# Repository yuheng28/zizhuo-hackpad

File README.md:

# ZizhuoPad

## Overview

ZizhuoPad is a custom mechanical macropad with 6 keys and an OLED display.

It is designed to allow for easy hotswapping of the switches, and (maybe not as easy) key mapping modifications.

## Rationale

This is a project to build a custom mechanical macropad. The purpose of this project is to create a birthday gift for my friend, after whom this project is named.

As a technical challenge, I opted to write the firmware using AVR-C, instead of using Arduino or QMK. The PCB was designed using KiCAD, and the case was designed using Fusion 360.

## Hardware Summary

### Electronics
- Microcontroller: SparkFun Pro Micro (ATmega32U4)
- OLED Display: 128x32 pixel display
- Switches: 6 hotswappable mechanical switches (Akko Piano Switches)
- Connector: USB-C

### Case
- Material: PETG
- Infill: 75%
- Walls: 10 for Case, 5 for Lid
- Layer Height: 0.2mm

## Modifying the Software

In the `firmware` directory, a Microchip Studio project is included. You can open the `.atsln` file in Microchip Studio to build the firmware.

The firmware uses the LUFA library to implement USB HID functionality. The project was first developed using the LUFA library's keyboard example, so as to have the build environment set up and working. Then, the code was modified to implement the desired functionality for the macropad.

However, since these are all in the project files, the build environment is already set up and working.

To modify the key mappings, lines 292-325 in Keyboard.c can be modified by replacing the keycode macros with the appropriate keycodes from LUFA's HID usage tables.

To modify the animation on the OLED display, the lines 65-135 in OLED.c can be modified with the appropriate bytes to display the desired animation. The OLED display has a resolution of 128x32 pixel display. To generate the byte array for the animation, use [Javl's image2cpp tool](https://javl.github.io/image2cpp/). The relevant settings for the tool are:
- Canvas Size: 128x32
- Orientation: Vertical
- Invert pixels: Yes (alternatively, line 191 in Keyboard.c can be commented to invert the pixels)

The other settings can be left as their default values. The generated byte array can then be copied into lines 292-325 in Keyboard.c.

After building the firmware, the resulting `Keyboard.hex` file can be flashed to the ATmega32U4 microcontroller using avrdude.

To flash the microcontroller, it needs to first be put into bootloader mode. This can be done by shorting the reset pin to ground. For approximately 8 seconds after doing this, the microcontroller will be in bootloader mode and can be flashed using avrdude.

## Project Pictures

## Special Thanks

- [Boyce Ang Kok Hong (Hong Guo Feng)]() for helping with the design of the case, as well as providing help every step of the way.
- [HackClub](https://hackclub.com/) for inspiring this project
- [Javl's image2cpp tool](https://javl.github.io/image2cpp/) for generating the byte array for the OLED animation
- [LUFA library](https://www.fourwalledcubicle.com/LUFA.php) for providing the USB HID functionality
- [Sun Zizhuo](https://github.com/UnidentifiedX) for giving us a reason to make this project in the first place

## Bill of Materials
| **Name**                          | **Quantity** | **Price** | **Link**                                                                                                                                                     | **Distributor** |
|-----------------------------------|--------------|-----------|--------------------------------------------------------------------------------------------------------------------------------------------------------------|-----------------|
| 3D Printed Case                   | 1            | 0         |                                                                                                                                                              | Additive Inn    |
| USB C Cable                       | 1            | 0         |                                                                                                                                                              | Selleys         |
| Gateron Hot-swappable Key Sockets | 6            | 0         | https://shopee.sg/10-pcs-Gateron-Hot-swappable-PCB-Socket-Mechanical-Keyboard-DIY-Hot-Plug-Socket-For-Cherry-MX-Switch-i.890923955.26713298801               | Shopee          |
| Resistors (1k)                    | 2            | 0         | https://shopee.sg/1-PCS-or-10-PCS-of-Metal-Film-Resistors-1-4W-0.25W-1-10-Ohm-~1M-Ohm-Perintang-i.1361674071.27680985111                                     | Shopee          |
| Resistors (4.7k)                  | 6            | 0         | https://shopee.sg/1-PCS-or-10-PCS-of-Metal-Film-Resistors-1-4W-0.25W-1-10-Ohm-~1M-Ohm-Perintang-i.1361674071.27680985111                                     | Shopee          |
| 0.91" 128x32 OLED Display         | 1            | 0         | https://shopee.sg/White-Blue-color-128X64-OLED-LCD-LED-Display-Module-For-Arduino-0.91-0.96-1.3-I2C-IIC-Serial-new-original-with-Case-i.365165105.8999544279 | Shopee          |
| PCB                               | 1            | 0         |                                                                                                                                                              | JLCPCB          |
| Akko Piano Switches               | 6            | 0         | https://shopee.sg/-LINEAR-Akko-V3-Piano-Pro-45gf-Linear-Factory-Lubed-Mechanical-Switch-i.1344447555.27310390752                                             | Shopee          |
| Sparkfun Pro Micro                | 1            | 0         | https://shopee.sg/Pro-Micro-ATmega32U4-5V-16MHz-Replace-ATmega328-For-ATMega-32U4-Pro-Mini-With-2-Row-Pin-Header-i.517411014.23679394357                     | Shopee          |

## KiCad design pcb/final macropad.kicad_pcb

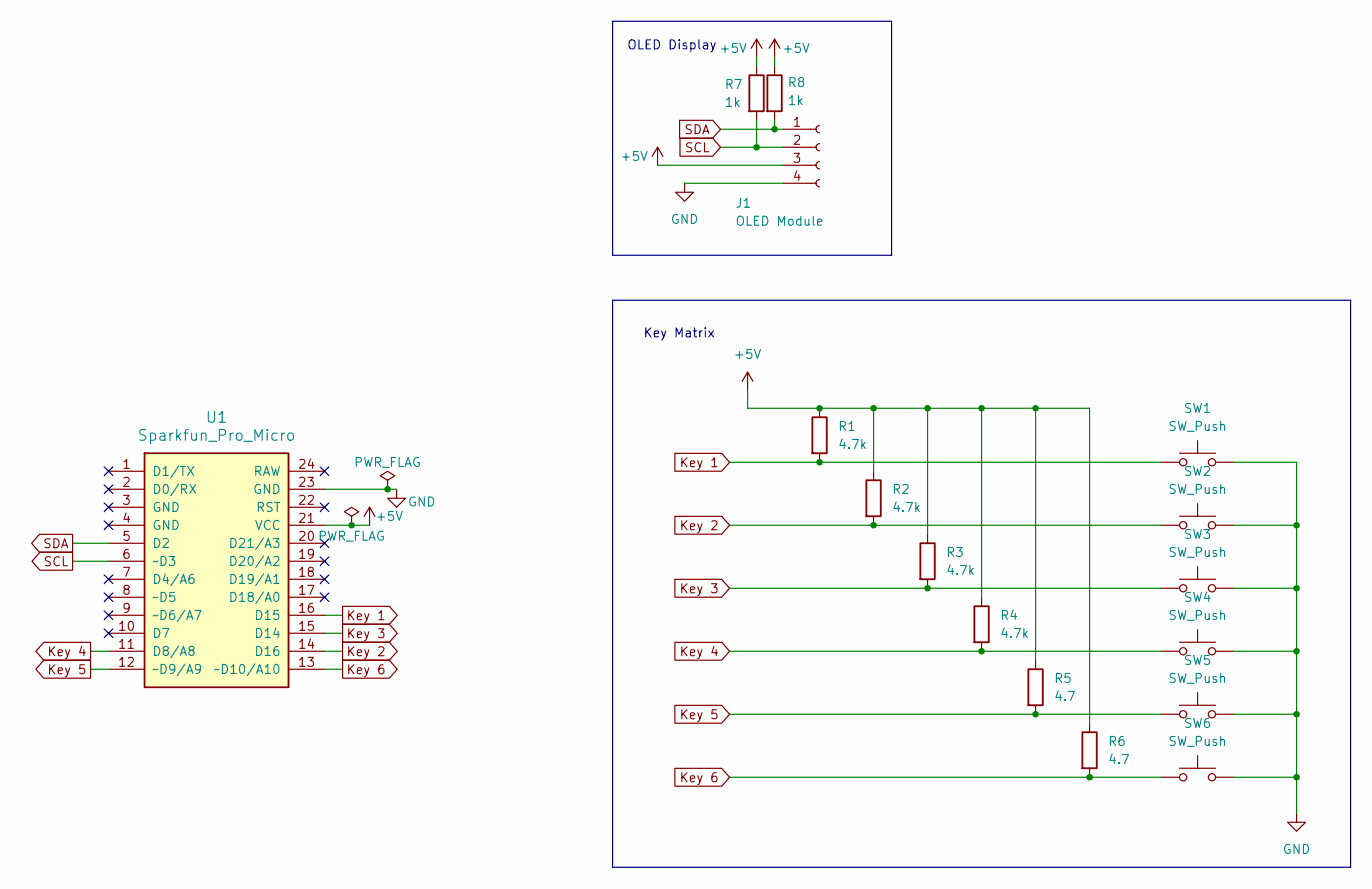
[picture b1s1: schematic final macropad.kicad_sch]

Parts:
J1: OLED Module; PinSocket_1x04_P2.54mm_Vertical
R1, R2, R3, R4: 4.7k; R_Axial_DIN0207_L6.3mm_D2.5mm_P7.62mm_Horizontal
R5, R6: 4.7; R_Axial_DIN0207_L6.3mm_D2.5mm_P7.62mm_Horizontal
R7, R8: 1k; R_Axial_DIN0207_L6.3mm_D2.5mm_P7.62mm_Horizontal
SW1, SW2, SW3, SW4, SW5, SW6: SW_Push; MXOnly-1U-Hotswap
U1: Sparkfun_Pro_Micro

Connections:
+5V: J1.3, R1.1, R2.1, R3.1, R4.1, R5.1, R6.1, R7.1, R8.1, U1.21 (VCC)
GND: J1.4, SW1.2, SW2.2, SW3.2, SW4.2, SW5.2, SW6.2, U1.23 (GND)
Key 1: R1.2, SW1.1, U1.16 (D15)
Key 2: R2.2, SW2.1, U1.14 (D16)
Key 3: R3.2, SW3.1, U1.15 (D14)
Key 4: R4.2, SW4.1, U1.11 (D8/A8)
Key 5: R5.2, SW5.1, U1.12 (~D9/A9)
Key 6: R6.2, SW6.1, U1.13 (~D10/A10)
SCL: J1.2, R7.2, U1.6 (~D3)
SDA: J1.1, R8.2, U1.5 (D2)

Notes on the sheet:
Key Matrix
OLED Display

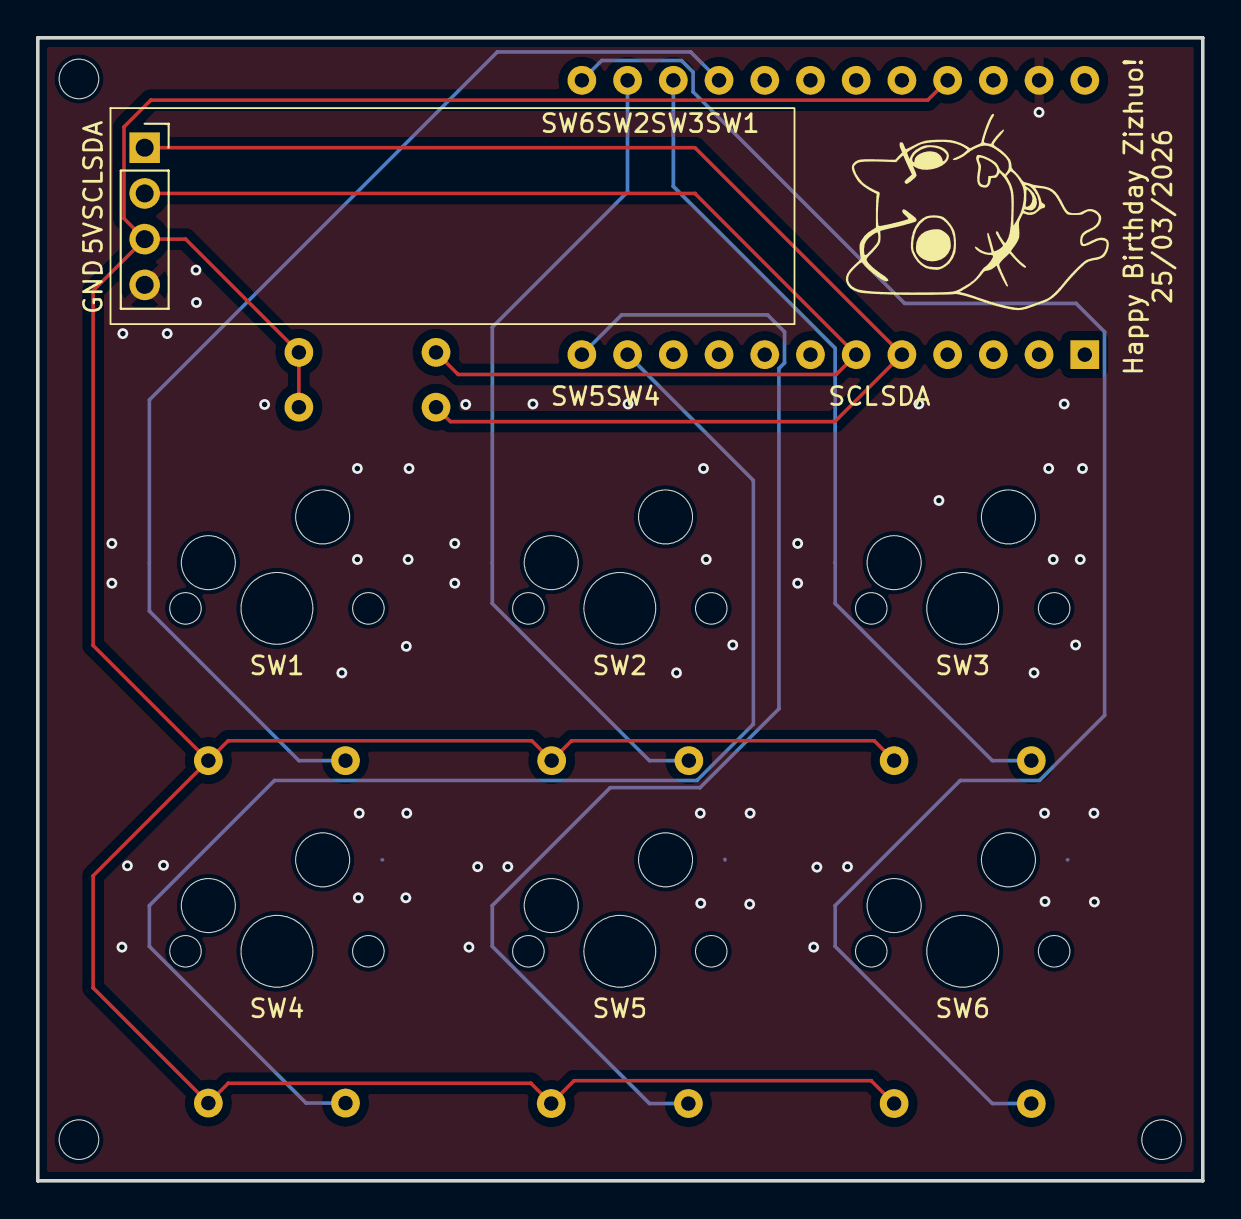
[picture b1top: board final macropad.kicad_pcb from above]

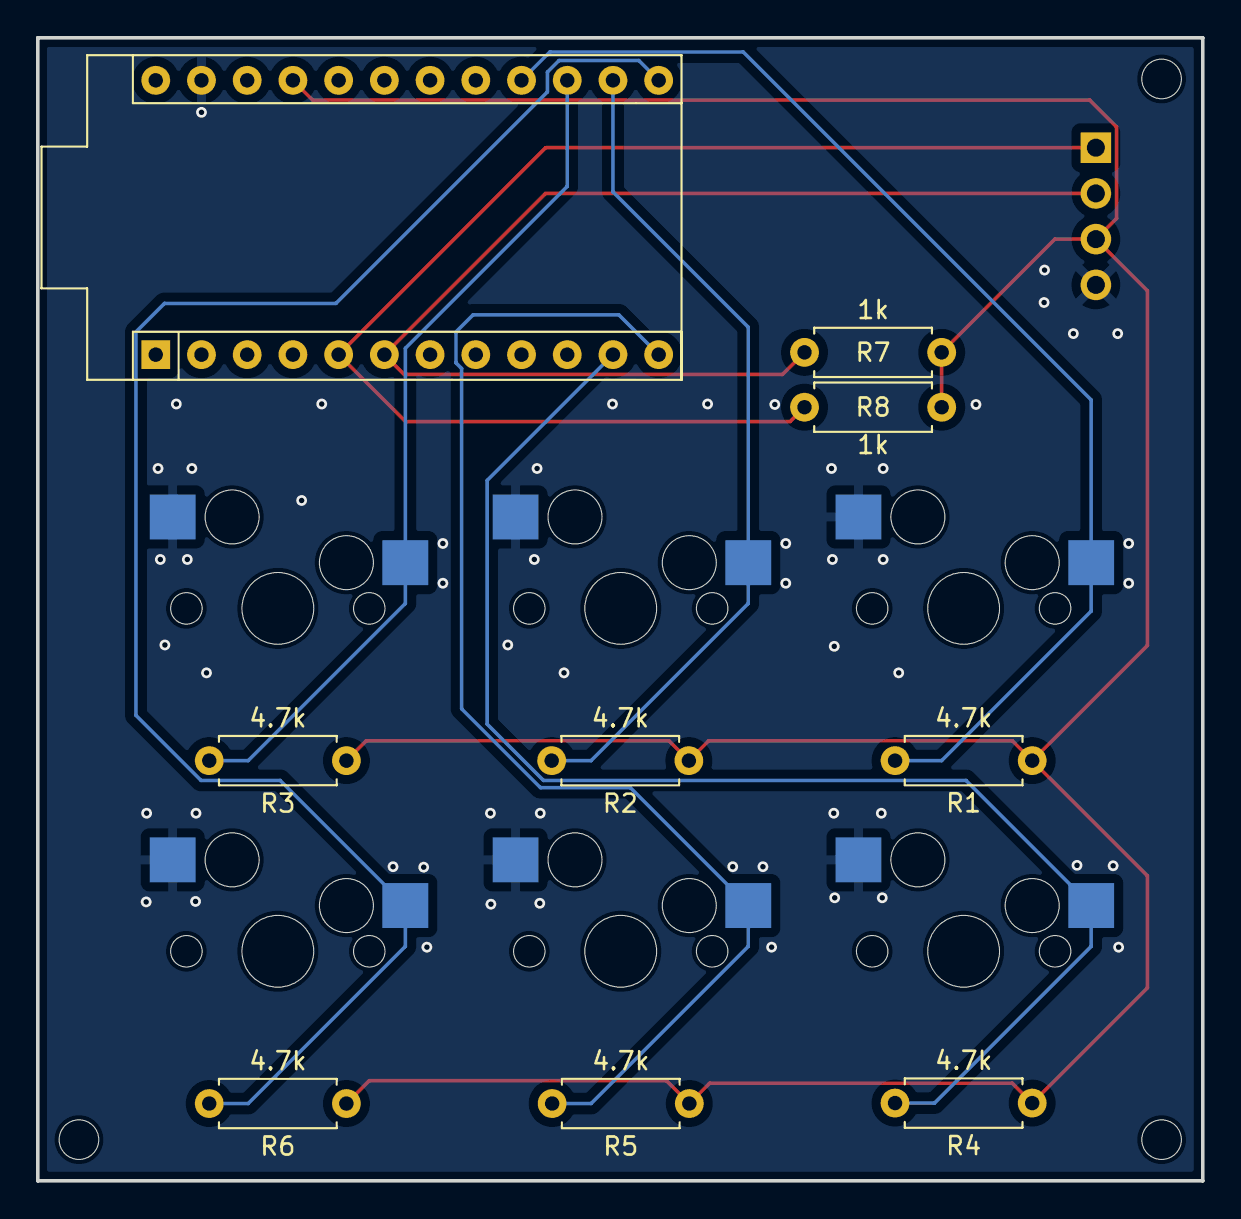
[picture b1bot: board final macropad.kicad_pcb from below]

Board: 2 copper layers, 64.7 x 63.5 mm, 16 parts (9 on the bottom side), 10 nets.

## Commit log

2026-04-06 replaced footprints of switches, routed pcb
2026-04-10 Added models
2026-04-10 redesigned PCB, added silkscreen
2026-04-11 Added firmware
2026-04-13 updated pcb
2026-04-13 updated pcb, removed old firmware from tracking
2026-04-13 Working Firmware (for keyboard)
2026-04-14 finished oled drivers
2026-04-15 working on firmware, i2c does not want to work nicely with the usb process
2026-04-16 finished up firmware
2026-04-19 changed the display to run as a 128x32 display instead. Inverted colours
2026-04-19 added gerber files
2026-04-21 updated drawing sheet
2026-05-02 final additions
2026-05-16 forgot to include the price in the bom
